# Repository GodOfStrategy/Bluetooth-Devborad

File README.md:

# Custom Bluetooth Devboard 
This is a cutom bluetooth devboard made by me for IoT and short range communication and automation. 
This board uses a nRF 52840 QIAA-F-R7 along with a RP2040 for processing, wired together with SPI.
It also uses 2 crystals 12MHz and 32 MHz for thr Rp 2040 and the nRF 52840 respectively.
A TLV75533PDBV (LDO) as my Voltage regulator.
2 USB-C receptacles for programming both chips with firmware.
SMD resistors.
SMD capacitors.
Here is my schematic:

Here is my PCB:

Here is the 3D Imge of my PCB:

Here is my BoM of PCB components:
[BLE_DEV_001_bom.csv](https://github.com/user-attachments/files/30661502/BLE_DEV_001_bom.csv)

Please find all production and firmware files in my repo.

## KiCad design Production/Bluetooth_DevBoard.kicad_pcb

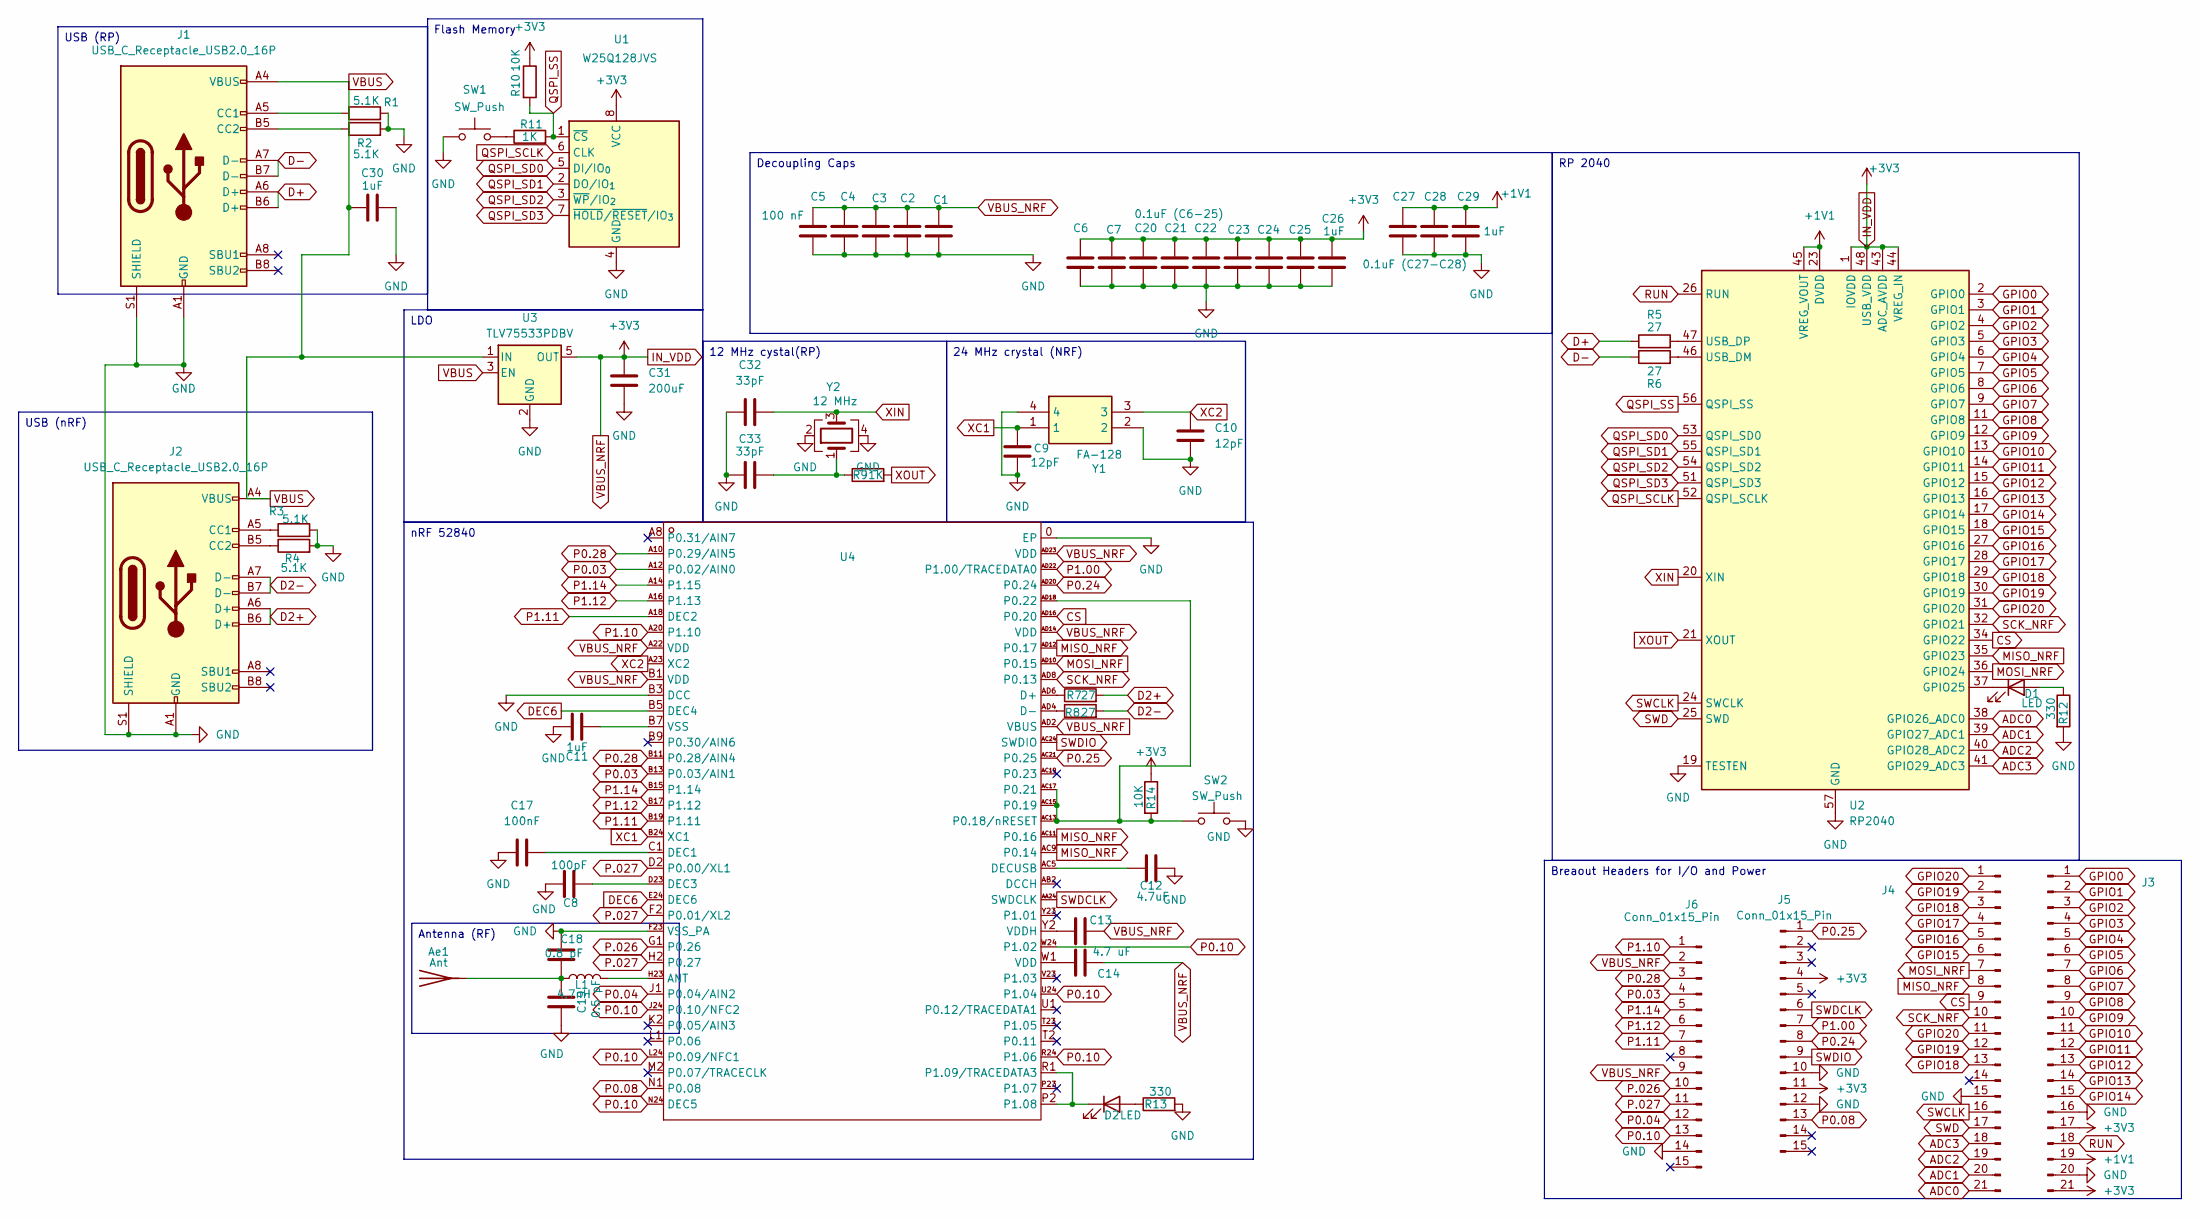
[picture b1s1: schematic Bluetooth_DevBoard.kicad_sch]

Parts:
Ae1: Ant; PinSocket_1x01_P2.54mm_Vertical
C1, C2, C3, C4, C5: 100 nF; C_0402_1005Metric
C6: 0.1uF (C6-25); C_0402_1005Metric
C7, C20, C21, C22, C23, C24, C25, C27: 0.1uF; C_0402_1005Metric
C8: 100pF; C_0402_1005Metric
C9, C10: 12pF; C_0402_1005Metric
C11, C26, C28, C30: 1uF; C_0402_1005Metric
C12: 4.7uF; C_0402_1005Metric
C13, C14: 4.7 uF; C_0402_1005Metric
C17: 100nF; C_0402_1005Metric
C18: 0.8 pF; C_0402_1005Metric
C19: 0.5 pF; C_0402_1005Metric
C29: 0.1uF (C27-C28); C_0402_1005Metric
C31: 200uF; C_1206_3216Metric
C32, C33: 33pF; C_0402_1005Metric
D1, D2: LED; D_0402_1005Metric
J1, J2: USB_C_Receptacle_USB2.0_16P; USB_C_Receptacle_HCTL_HC-TYPE-C-16P-01A
J3: Conn_01x21_Pin(RP); PinHeader_1x21_P2.54mm_Vertical
J4: Conn_01x21_Pin (RP); PinHeader_1x21_P2.54mm_Vertical
J5, J6: Conn_01x15_Pin; PinHeader_1x15_P2.54mm_Vertical
L1: 4.7nH; L_0402_1005Metric
R1, R2, R3, R4: 5.1K; R_0402_1005Metric
R5, R6, R7, R8: 27; R_0402_1005Metric
R9, R11: 1K; R_0402_1005Metric
R10, R14: 10K; R_0402_1005Metric
R12, R13: 330; R_0402_1005Metric
SW1, SW2: SW_Push; SW_SPST_PTS647_Sx38
U1: W25Q128JVS; SOIC-8_5.3x5.3mm_P1.27mm
U2: RP2040; QFN-56-1EP_7x7mm_P0.4mm_EP3.2x3.2mm
U3: TLV75533PDBV; SOT-23-5
U4: QIAA-F-R7; Manufacturer Part NRF52840-QIAA-F-R7; LCSC Part Name NRF52840-QIAA-F-R7
Y1: FA-128; FA128; Manufacturer_Part_Number Q22FA12800025 FA-128 32 MHZ 8.0PF
Y2: 12 MHz; Crystal_SMD_3225-4Pin_3.2x2.5mm

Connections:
+1V1: C27.1, C28.1, C29.1, J3.19, U2.23 (DVDD), U2.45 (VREG_VOUT), U2.50 (DVDD)
ADC0: J4.21, U2.38 (GPIO26_ADC0)
ADC1: J4.20, U2.39 (GPIO27_ADC1)
ADC2: J4.19, U2.40 (GPIO28_ADC2)
ADC3: J4.18, U2.41 (GPIO29_ADC3)
CS: J4.9, U2.34 (GPIO22), U4.AD16 (P0.20)
D2+: J2.A6 (D+), J2.B6 (D+), R7.2
D2-: J2.A7 (D-), J2.B7 (D-), R8.2
D+: J1.A6 (D+), J1.B6 (D+), R5.1
D-: J1.A7 (D-), J1.B7 (D-), R6.1
DEC6: U4.B5 (DEC4), U4.E24 (DEC6)
GND: C1.2, C2.2, C3.2, C4.2, C5.2, C6.2, C7.2, C8.2, C9.1, C10.2, C11.1, C12.2, C17.1, C18.2, C19.1, C20.2, C21.2, C22.2, C23.2, C24.2, C25.2, C26.2, C27.2, C28.2, C29.2, C30.2, C31.1, C32.1, C33.1, J1.A1 (GND), J1.A12 (GND), J1.B1 (GND), J1.B12 (GND), J1.S1 (SHIELD), J2.A1 (GND), J2.A12 (GND), J2.B1 (GND), J2.B12 (GND), J2.S1 (SHIELD), J3.16, J3.20, J4.15, J5.10, J5.12, J6.14, R1.2, R2.2, R3.2, R4.2, R12.2, R13.2, SW1.1, SW2.2, U1.4 (GND), U2.19 (TESTEN), U2.57 (GND), U3.2 (GND), U4.0 (EP), U4.B3 (DCC), U4.F23 (VSS_PA), Y1.2, Y1.4, Y2.2, Y2.4; also elsewhere on the board
GPIO0: J3.1, U2.2 (GPIO0)
GPIO1: J3.2, U2.3 (GPIO1)
GPIO2: J3.3, U2.4 (GPIO2)
GPIO3: J3.4, U2.5 (GPIO3)
GPIO4: J3.5, U2.6 (GPIO4)
GPIO5: J3.6, U2.7 (GPIO5)
GPIO6: J3.7, U2.8 (GPIO6)
GPIO7: J3.8, U2.9 (GPIO7)
GPIO8: J3.9, U2.11 (GPIO8)
GPIO9: J3.10, U2.12 (GPIO9)
GPIO10: J3.11, U2.13 (GPIO10)
GPIO11: J3.12, U2.14 (GPIO11)
GPIO12: J3.13, U2.15 (GPIO12)
GPIO13: J3.14, U2.16 (GPIO13)
GPIO14: J3.15, U2.17 (GPIO14)
GPIO15: J4.6, U2.18 (GPIO15)
GPIO16: J4.5, U2.27 (GPIO16)
GPIO17: J4.4, U2.28 (GPIO17)
GPIO18: J4.3, J4.13, U2.29 (GPIO18)
GPIO19: J4.2, J4.12, U2.30 (GPIO19)
GPIO20: J4.1, J4.11, U2.31 (GPIO20)
IN_VDD: C1.1, C2.1, C3.1, C4.1, C5.1, C6.1, C7.1, C13.2, C14.1, C20.1, C21.1, C22.1, C23.1, C24.1, C25.1, C26.1, C31.2, J3.17, J3.21, J5.4, J5.11, J6.2, J6.9, R10.1, R14.1, U1.8 (VCC), U2.1 (IOVDD), U2.10 (IOVDD), U2.22 (IOVDD), U2.33 (IOVDD), U2.42 (IOVDD), U2.43 (ADC_AVDD), U2.44 (VREG_IN), U2.48 (USB_VDD), U2.49 (IOVDD), U3.5 (OUT), U4.A22 (VDD), U4.AD2 (VBUS), U4.AD14 (VDD), U4.AD23 (VDD), U4.B1 (VDD)
MISO_NRF: J4.8, U2.35 (GPIO23), U4.AC9 (P0.14), U4.AC11 (P0.16), U4.AD12 (P0.17)
MOSI_NRF: J4.7, U2.36 (GPIO24), U4.AD10 (P0.15)
unnamed: Ae1.1 (A), C18.1, C19.2, L1.1
unnamed: C14.2, U4.W1 (VDD)
unnamed: C33.2, R9.1, Y2.1
unnamed: D1.2 (A), R12.1
unnamed: D1.1 (K), U2.37 (GPIO25)
unnamed: D2.2 (A), R13.1
unnamed: D2.1 (K), U4.P2 (P1.08), U4.R1 (P1.09/TRACEDATA3)
unnamed: J1.A5 (CC1), R1.1
unnamed: J1.B5 (CC2), R2.1
unnamed: J2.A5 (CC1), R3.1
unnamed: J2.B5 (CC2), R4.1
unnamed: R11.1, SW1.2
unnamed: R6.2, U2.46 (USB_DM)
unnamed: R5.2, U2.47 (USB_DP)
unnamed: L1.2, U4.H23 (ANT)
unnamed: R7.1, U4.AD6 (D+)
unnamed: R8.1, U4.AD4 (D-)
unnamed: C17.2, U4.C1 (DEC1)
unnamed: C8.1, U4.D23 (DEC3)
unnamed: C12.1, U4.AC5 (DECUSB)
unnamed 56: R14.2, SW2.1, U4.AC13 (P0.18/nRESET), U4.AC15 (P0.19), U4.AC17 (P0.21), U4.AD18 (P0.22); also elsewhere on the board
unnamed: C13.1, U4.Y2 (VDDH)
unnamed: C11.2, U4.B7 (VSS)
P0.03: J6.4, U4.A12 (P0.02/AIN0), U4.B13 (P0.03/AIN1)
P0.04: J6.12, U4.J1 (P0.04/AIN2)
P0.08: J5.13, U4.N1 (P0.08)
P0.10: J6.13, U4.J24 (P0.10/NFC2), U4.L24 (P0.09/NFC1), U4.N24 (DEC5), U4.R24 (P1.06), U4.U24 (P1.04), U4.W24 (P1.02)
P0.24: J5.8, U4.AD20 (P0.24)
P0.25: J5.1, U4.AC21 (P0.25)
P0.28: J6.3, U4.A10 (P0.29/AIN5), U4.B11 (P0.28/AIN4)
P1.00: J5.7, U4.AD22 (P1.00/TRACEDATA0)
P1.10: J6.1, U4.A20 (P1.10)
P1.11: J6.7, U4.A18 (DEC2), U4.B19 (P1.11)
P1.12: J6.6, U4.A16 (P1.13), U4.B17 (P1.12)
P1.14: J6.5, U4.A14 (P1.15), U4.B15 (P1.14)
P.026: J6.10, U4.G1 (P0.26)
P.027: J6.11, U4.D2 (P0.00/XL1), U4.F2 (P0.01/XL2), U4.H2 (P0.27)
QSPI_SCLK: U1.6 (CLK), U2.52 (QSPI_SCLK)
QSPI_SD0: U1.5 (DI/IO_{0}), U2.53 (QSPI_SD0)
QSPI_SD1: U1.2 (DO/IO_{1}), U2.55 (QSPI_SD1)
QSPI_SD2: U1.3 (~WP/IO_{2}), U2.54 (QSPI_SD2)
QSPI_SD3: U1.7 (~HOLD/~RESET/IO_{3}), U2.51 (QSPI_SD3)
QSPI_SS: R10.2, R11.2, U1.1 (~CS), U2.56 (QSPI_SS)
RUN: J3.18, U2.26 (RUN)
SCK_NRF: J4.10, U2.32 (GPIO21), U4.AD8 (P0.13)
SWCLK: J4.16, U2.24 (SWCLK)
SWD: J4.17, U2.25 (SWD)
SWDCLK: J5.6, U4.AA24 (SWDCLK)
SWDIO: J5.9, U4.AC24 (SWDIO)
VBUS: C30.1, J1.A4 (VBUS), J1.A9 (VBUS), J1.B4 (VBUS), J1.B9 (VBUS), J2.A4 (VBUS), J2.A9 (VBUS), J2.B4 (VBUS), J2.B9 (VBUS), U3.1 (IN), U3.3 (EN)
XC1: C9.2, U4.B24 (XC1), Y1.1
XC2: C10.1, U4.A23 (XC2), Y1.3
XIN: C32.2, U2.20 (XIN), Y2.3
XOUT: R9.2, U2.21 (XOUT)

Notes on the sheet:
Decoupling Caps
Flash Memory
USB (RP)
Antenna (RF)
USB (nRF)
12 MHz cystal(RP)
24 MHz crystal (NRF)
LDO
RP 2040
Breaout Headers for I/O and Power
nRF 52840

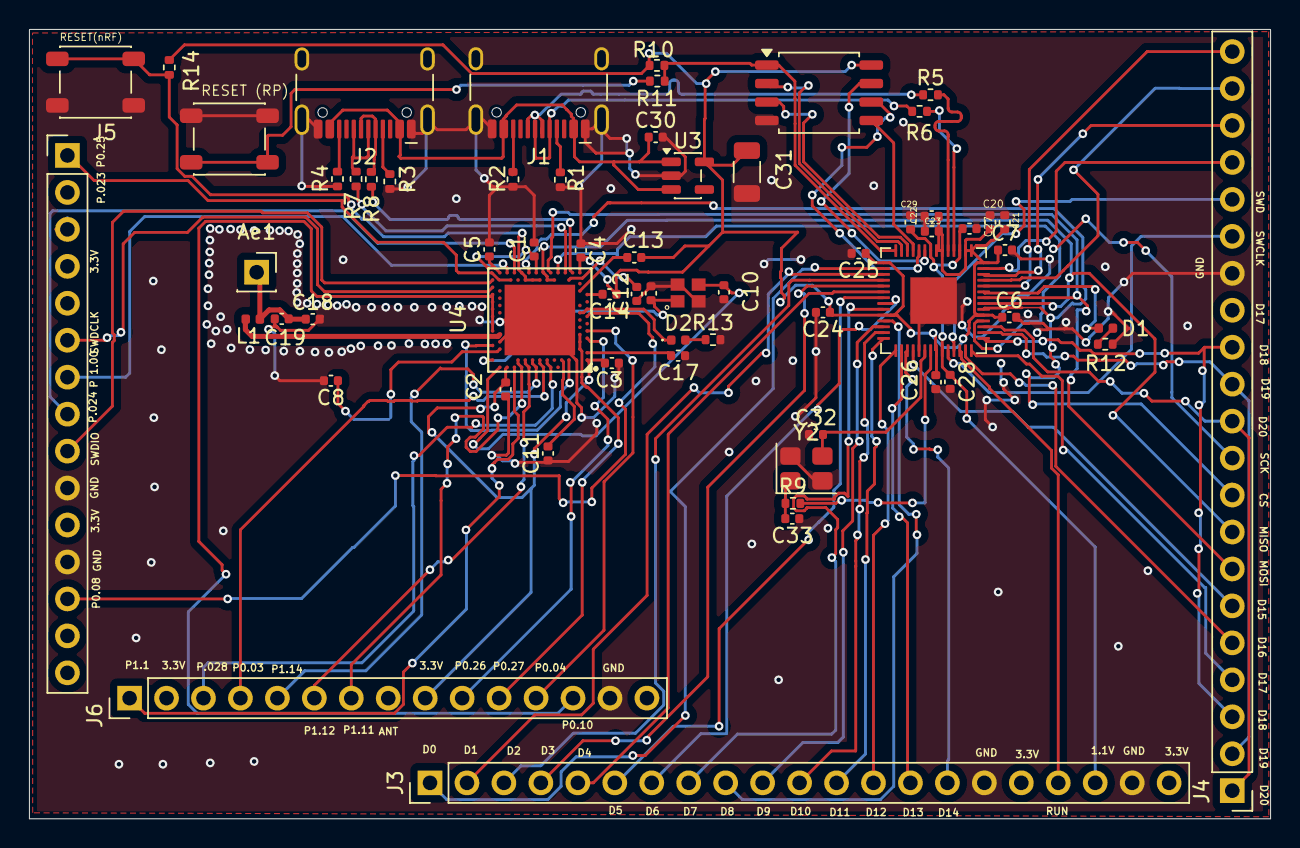
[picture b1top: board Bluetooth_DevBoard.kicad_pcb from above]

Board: 4 copper layers, 85.3 x 54.2 mm, 63 parts (0 on the bottom side), 90 nets.

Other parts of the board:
RESET(nRF): SW_Push; SW_SPST_PTS647_Sx38

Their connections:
GND: RESET(nRF).2; also elsewhere on the board
unnamed 56: RESET(nRF).1; also elsewhere on the board

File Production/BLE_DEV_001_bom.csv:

Designator,Footprint,Quantity,Value,LCSC Part #
AE1,PinSocket_1x01_P2.54mm_Vertical,1,Ant,
"C1, C2, C3, C4, C5",0402,5,100 nF,
"C10, C9",0402,2,12pF,
"C11, C26, C28, C30",0402,4,1uF,
C12,0402,1,4.7uF,
"C13, C14",0402,2,4.7 uF,
C17,0402,1,100nF,
C18,0402,1,0.8 pF,
C19,0402,1,0.5 pF,
"C20, C21, C22, C23, C24, C25, C27, C7",0402,8,0.1uF,
C29,0402,1,0.1uF (C27-C28),
C31,0402,1,200uF,
"C32, C33",0402,2,33pF,
C6,0402,1,0.1uF (C6-25),
C8,0402,1,100pF,
"D1, D2",0402,2,LED,
"J1, J2",USB_C_Receptacle_HRO_TYPE-C-31-M-12,2,USB_C_Receptacle_USB2.0_14P,
J3,PinHeader_1x21_P2.54mm_Vertical,1,Conn_01x21_Pin(RP),
J4,PinHeader_1x21_P2.54mm_Vertical,1,Conn_01x21_Pin (RP),
"J5, J6",PinHeader_1x15_P2.54mm_Vertical,2,Conn_01x15_Pin,
L1,0402,1,4.7nH,
"R1, R2, R3, R4",0402,4,5.1K,
"R10, R14",0402,2,10K,
"R11, R9",0402,2,1K,
"R12, R13",0402,2,330,
"R5, R6, R7, R8",0402,4,27,
"RESET(NRF), SW1",SW_SPST_PTS647_Sx38,2,SW_Push,
U1,SOIC-8_5.3x5.3mm_P1.27mm,1,W25Q128JVS,
U2,QFN-56-1EP_7x7mm_P0.4mm_EP3.2x3.2mm,1,RP2040,
U3,SOT-23-5,1,TLV75533PDBV,
U4,QIAA-F-R7,1,~,
Y1,FA128,1,FA-128,
Y2,Crystal_SMD_3225-4Pin_3.2x2.5mm,1,12 MHz,

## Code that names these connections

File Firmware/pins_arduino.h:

#pragma once

// Pin definitions taken from:
//    https://datasheets.raspberrypi.org/pico/pico-datasheet.pdf

// LEDs


// Serial
#define PIN_SERIAL1_TX (0u)
#define PIN_SERIAL1_RX (1u)

#define PIN_SERIAL2_TX (8u)
#define PIN_SERIAL2_RX (9u)

// SPI0 pins (required by common.h)
#define PIN_SPI0_SS    (22u)  // CS
#define PIN_SPI0_MOSI  (24u)  // MOSI_NRF
#define PIN_SPI0_MISO  (23u)  // MISO_NRF
#define PIN_SPI0_SCK   (21u)  // SCK_NRF




// Leave SPI1 as default (unused in your schematic)
#define PIN_SPI1_MISO  (12u)
#define PIN_SPI1_MOSI  (15u)
#define PIN_SPI1_SCK   (14u)
#define PIN_SPI1_SS    (13u)

// Wire
#define PIN_WIRE0_SDA  (4u)
#define PIN_WIRE0_SCL  (5u)

#define PIN_WIRE1_SDA  (26u)
#define PIN_WIRE1_SCL  (27u)

#define SERIAL_HOWMANY (3u)
#define SPI_HOWMANY    (2u)
#define WIRE_HOWMANY   (2u)

#include "../generic/common.h"

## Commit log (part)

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2026-05-04 Create a
